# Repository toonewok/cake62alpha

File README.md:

# Materials
2x RP2040-zero waveshare  
1x Left PCB  
1x Right PCB  
1x Top Left Case  
1x Bottom Left Case (100%infill)  
1x Top Right Case  
1x Bottom Right Case (100%infill)  
2x STX-3000  
62x chocv1 or mx hotswaps  
62x chocv1 or mx switches  
14x M2x6 screws
14x M2 brass inserts  
1x TRS 3.5mm cable  
1x USB C cable  
2.54mm pinheaders(male)  
2mm foam(optional)  
<br>

# Assembly
<p>Assembly is relatively self-explanatory, the only thing to call out is that you will need to solder a patch wire from pin 28 to pin 8. The yellow path on the following image will show you where that is(I do this on the bottom side of the PCB after attaching the RP2040 to the PCB) -</p>  
  
<br>

# Code/Firmware
<p>It needs to be stated that under no cirumstances are you to mess with the TRS jack while either half is powered, doing so could result in shorting the halves.</p> <p>Start by plugging in the halves one at a time individually, they will first appear as 'RPI-RP2' in your file browser, you will need to obtain the latest version of circuitpython for the RP2040 waveshare from the <a href="https://circuitpython.org/downloads">circuitpython downloads page.</a> Drag and drop that onto to the root of the device and it should disconnect, after a few seconds it should reappear as 'CIRCUITPY'. Now you need the most recent version of <a href="https://github.com/KMKfw/kmk_firmware/archive/refs/heads/main.zip">KMK.</a> Unzip the KMK folder and enter it, take the 'kmk' folder and drag it to the root of the RP2040. Depending on which half you are setting up take the respective code.py.X and place it on the root of the RP2040 as just 'code.py'....done:)</p>  
<br>
<p>Any keymap changes are made in the code.py, be sure to modify both halves</p>

# Default Keymap

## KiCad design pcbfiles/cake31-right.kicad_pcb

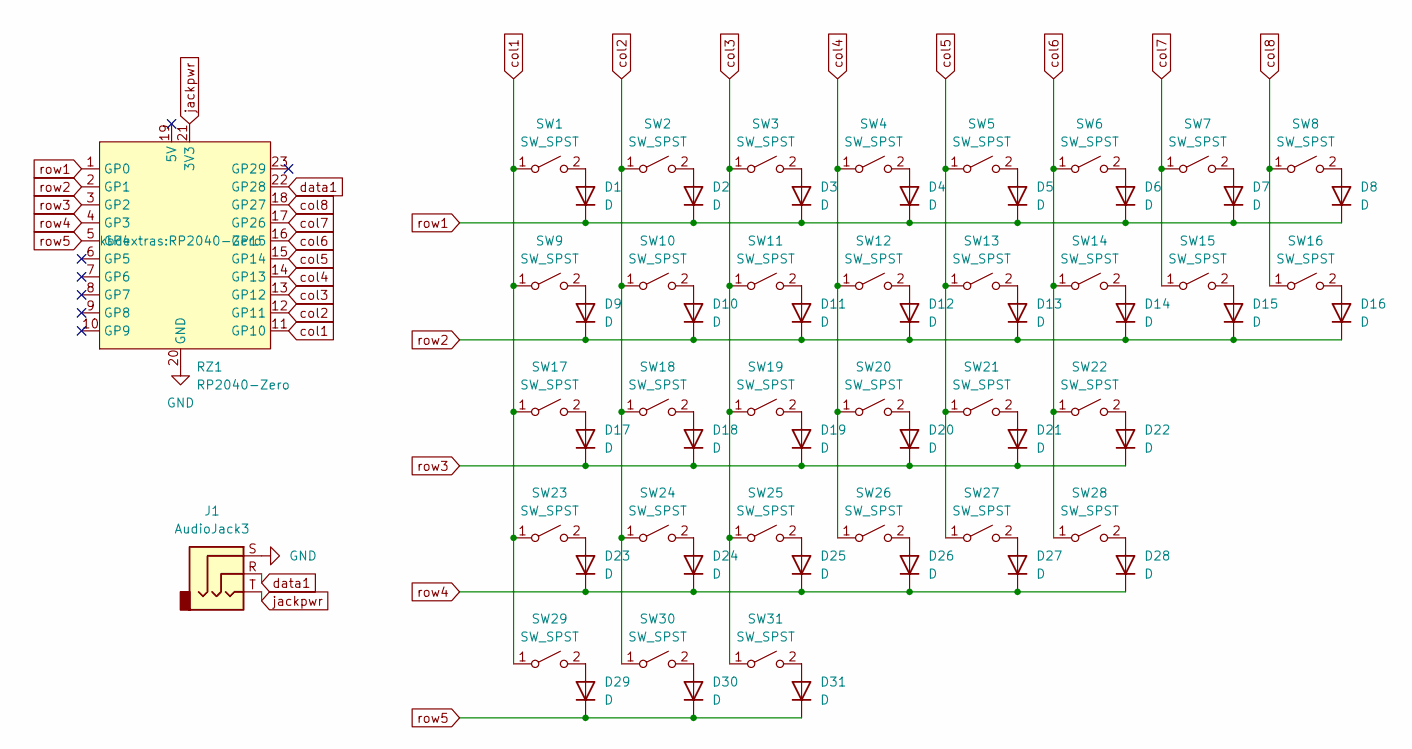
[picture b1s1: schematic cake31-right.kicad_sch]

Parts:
D1, D2, D3, D4, D5, D6, D7, D8, D9, D10, D11, D12, D13, D14, D15, D16, D17, D18, D19, D20, D21, D22, D23, D24, D25, D26, D27, D28, D29, D30, D31: D; 1N4148W
J1: AudioJack3; STX-3000
RZ1: RP2040-Zero
SW1, SW2, SW3, SW4, SW5, SW6, SW7, SW8, SW9, SW10, SW11, SW12, SW13, SW14, SW15, SW16, SW17, SW18, SW19, SW20, SW21, SW22, SW23, SW24, SW25, SW26, SW27, SW28, SW29, SW30, SW31: SW_SPST; mx-choc-dual

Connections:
GND: J1.S, RZ1.20 (GND)
unnamed: D1.2 (A), SW1.2 (B)
unnamed: D2.2 (A), SW2.2 (B)
unnamed: D3.2 (A), SW3.2 (B)
unnamed: D4.2 (A), SW4.2 (B)
unnamed: D5.2 (A), SW5.2 (B)
unnamed: D6.2 (A), SW6.2 (B)
unnamed: D7.2 (A), SW7.2 (B)
unnamed: D8.2 (A), SW8.2 (B)
unnamed: D9.2 (A), SW9.2 (B)
unnamed: D10.2 (A), SW10.2 (B)
unnamed: D11.2 (A), SW11.2 (B)
unnamed: D12.2 (A), SW12.2 (B)
unnamed: D13.2 (A), SW13.2 (B)
unnamed: D14.2 (A), SW14.2 (B)
unnamed: D15.2 (A), SW15.2 (B)
unnamed: D16.2 (A), SW16.2 (B)
unnamed: D17.2 (A), SW17.2 (B)
unnamed: D18.2 (A), SW18.2 (B)
unnamed: D19.2 (A), SW19.2 (B)
unnamed: D20.2 (A), SW20.2 (B)
unnamed: D21.2 (A), SW21.2 (B)
unnamed: D22.2 (A), SW22.2 (B)
unnamed: D23.2 (A), SW23.2 (B)
unnamed: D24.2 (A), SW24.2 (B)
unnamed: D25.2 (A), SW25.2 (B)
unnamed: D26.2 (A), SW26.2 (B)
unnamed: D27.2 (A), SW27.2 (B)
unnamed: D28.2 (A), SW28.2 (B)
unnamed: D29.2 (A), SW29.2 (B)
unnamed: D30.2 (A), SW30.2 (B)
unnamed: D31.2 (A), SW31.2 (B)
col1: RZ1.11 (GP10), SW1.1 (A), SW9.1 (A), SW17.1 (A), SW23.1 (A), SW29.1 (A)
col2: RZ1.12 (GP11), SW2.1 (A), SW10.1 (A), SW18.1 (A), SW24.1 (A), SW30.1 (A)
col3: RZ1.13 (GP12), SW3.1 (A), SW11.1 (A), SW19.1 (A), SW25.1 (A), SW31.1 (A)
col4: RZ1.14 (GP13), SW4.1 (A), SW12.1 (A), SW20.1 (A), SW26.1 (A)
col5: RZ1.15 (GP14), SW5.1 (A), SW13.1 (A), SW21.1 (A), SW27.1 (A)
col6: RZ1.16 (GP15), SW6.1 (A), SW14.1 (A), SW22.1 (A), SW28.1 (A)
col7: RZ1.17 (GP26), SW7.1 (A), SW15.1 (A)
col8: RZ1.18 (GP27), SW8.1 (A), SW16.1 (A)
data1: J1.R, RZ1.22 (GP28)
jackpwr: J1.T, RZ1.21 (3V3)
row1: D1.1 (K), D2.1 (K), D3.1 (K), D4.1 (K), D5.1 (K), D6.1 (K), D7.1 (K), D8.1 (K), RZ1.1 (GP0)
row2: D9.1 (K), D10.1 (K), D11.1 (K), D12.1 (K), D13.1 (K), D14.1 (K), D15.1 (K), D16.1 (K), RZ1.2 (GP1)
row3: D17.1 (K), D18.1 (K), D19.1 (K), D20.1 (K), D21.1 (K), D22.1 (K), RZ1.3 (GP2)
row4: D23.1 (K), D24.1 (K), D25.1 (K), D26.1 (K), D27.1 (K), D28.1 (K), RZ1.4 (GP3)
row5: D29.1 (K), D30.1 (K), D31.1 (K), RZ1.5 (GP4)

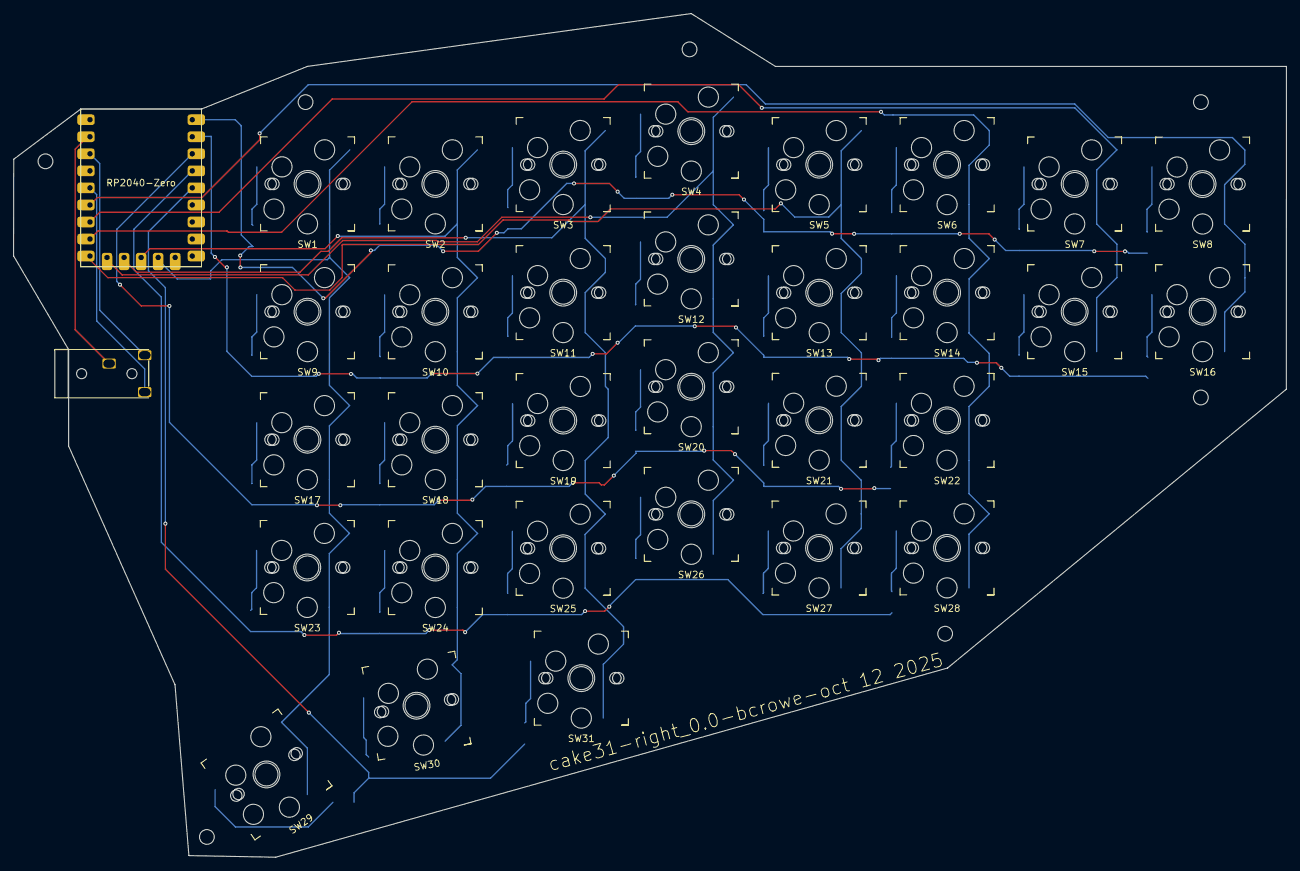
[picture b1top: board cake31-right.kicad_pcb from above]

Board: 2 copper layers, 189.6 x 125.7 mm, 64 parts (0 on the bottom side), 47 nets.

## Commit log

2025-11-01 yurrr
2025-11-01 fixing hyperlinks
2025-11-01 oops
2025-11-01 attempting to fix image
2025-11-01 take 2
2025-11-01 take3?
2025-11-01 fixed README
2025-11-01 those are infact not optional lol
2025-11-01 added specifics to what type of rp2040 to avoid confusion
2025-11-01 specified male pin headers
2025-11-03 modified the keymap and added an image of it cause why not
2025-11-03 forgot the >
2025-11-03 fixed f10
2025-11-03 made backspace alot 'bigger', thank me later
2025-11-03 fixed right shift on keymap.png
2025-11-03 had to add caps lock
2025-11-03 added easy plus and underscore
2025-11-05 there are some serious issues with the original keymap, this is a bit experimental but we'll see
2026-04-29 stl update, hi emma
